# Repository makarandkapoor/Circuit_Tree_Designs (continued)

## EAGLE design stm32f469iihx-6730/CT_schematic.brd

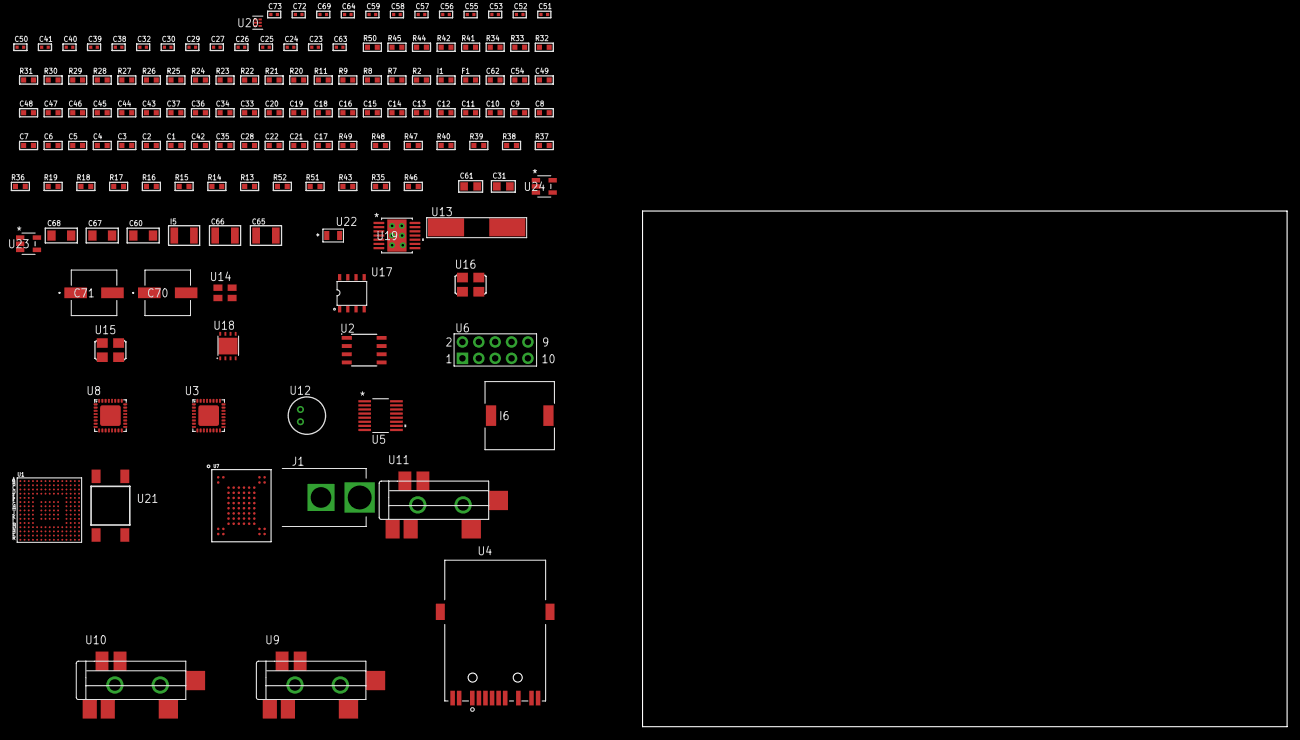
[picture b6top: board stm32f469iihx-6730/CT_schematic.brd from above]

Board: 2 copper layers, 100.0 x 80.0 mm, 147 parts (0 on the bottom side), 111 nets, no tracks yet.

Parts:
C1, C19, C33, C34, C36, C37, C43, C44, C45, C46, C47, C48, C49, C54, C62: 1e-06; C0603
C2, C3, C4, C5, C6, C7, C8, C9, C10, C11, C12, C13, C14, C15, C16, C20: 1e-07; C0603
C17: 4.7e-06; C0603
C18: 1e-08; C0603
C21, C22, C28, C42: 2.2e-06; C0603
C23, C24: 1e-11; C0402
C25, C55, C56, C57, C58, C59, C72, C73: 1e-08; C0402
C26, C27, C29, C30, C32, C38, C39, C40, C41, C50, C51, C52, C53, C64, C69: 1e-07; C0402
C31, C61: 1e-05; C0805
C35: 2.2e-07; C0603
C60, C67, C68: 1e-05; C1206
C63: 3.3e-09; C0402
C65, C66: 2.2e-05; C1210
C70, C71: 0.0001; EXV-9H
F1: 240.0; L0603
I1: 97.0; R0603
I5: 1e-05; L1210
I6: 5.2e-06; DR1040
J1: PJ-037B; PJ-037B_PACKAGE
R2, R29, R31, R32, R33, R34, R45: 1000.0; R0603
R7, R8, R25, R26, R27, R28, R30: 4700.0; R0603
R9, R11: 2200.0; R0603
R13, R14, R15, R16, R17, R18, R19, R36, R37, R38, R39, R40, R48, R49: 10000.0; R0603
R20, R21: 0.1; R0603
R22, R44: 200.0; R0603
R23: 220.0; R0603
R24: 6490.0; R0603
R35, R43: 100000.0; R0603
R41, R42: 1270.0; R0603
R46: 71007.101651032; R0603
R47: 22000.0; R0603
R50: 9100.0; R0603
R51: 680000.0; R0603
R52: 120000.0; R0603
U1: STM32F469IIH6; UFBGA176
U2: AT25020B-SSHL-T; SOIC-8
U3: KSZ8081RNBIA-TR; QFN-32
U4: 7498011122R
U5: LTC2804CGN-1#PBF; SSOP-16
U6: HTSS-105-01-G-D
U7: mt29f4g08abadah4; VFBGA-63
U8: SGTL5000XNAA3; QFN-32
U9, U10, U11: SJ-43515TS-SMT-TR
U12: WM-64PCT; WM-64PC
U13: ABLS-25.000MHZ-B2F-T
U14: ASEK-32.768KHz-ECST; ASEK
U15: ASFL-24.57MHZ-NCS; ASFL1
U16: ASFL1-50MHZ-NCS; ASFL1
U17: idt74fct38072; IDT74FCT38072
U18: LP3878SDX-ADJ/NOPB; WSON-8
U19: tps54225PWP; HTSSOP14
U20: TPS3895ADRYR; SON-6
U21: 4-1437565-2; SW_4-1437565-2
U22: Q65110A2395; LGM67K-G1J2-24-Z
U23, U24: nc7sz125m5x; NC7SZ125M5X

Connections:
CLK_CRYSTAL_U1_G1: C23.1, U1.G1, U13.1
CLK_CRYSTAL_U1_H1: C24.1, U1.H1, U13.2
CLK_U1_E1: U1.E1, U14.3
CLK_U1_N2: U1.N2, U17.7
CLK_U3_9: U3.9, U17.6
CLK_U8_21: U8.21, U15.3
CLK_U17_3: U16.3, U17.3
GND: C1.2, C2.2, C3.2, C4.2, C5.2, C6.2, C7.2, C8.2, C9.2, C10.2, C11.2, C12.2, C13.2, C14.2, C15.2, C16.2, C17.2, C18.2, C19.2, C20.2, C21.2, C22.2, C23.2, C24.2, C25.2, C26.2, C27.2, C28.2, C29.2, C30.2, C31.2, C32.2, C33.2, C34.2, C36.2, C37.2, C38.2, C39.2, C40.2, C41.2, C42.2, C50.2, C51.2, C52.2, C53.2, C54.2, C55.2, C56.2, C57.2, C58.2, C59.2, C60.2, C61.2, C62.2, C63.2, C65.2, C66.2, C67.2, C68.2, C69.2, C70.2, C71.2, C72.2, C73.2, J1.2, R2.2, R15.2, R16.2, R20.2, R21.2, R24.2, R26.2, R29.2, R31.2, R32.2, R33.2, R34.2, R42.2, R45.2, R47.2, R50.2, R52.2, U1.D5, U1.D7, U1.D8, U1.D9, U1.F2, U1.F6, U1.F7, U1.F8, U1.F9, U1.F10, U1.F12, U1.G2, U1.G6, U1.G7, U1.G8, U1.G9, U1.G10, U1.G12, U1.H6, U1.H7, U1.H8, U1.H9, U1.H10, U1.H12, U1.J6, U1.J7, U1.J8, U1.J9, U1.J10, U1.K6, U1.K7, U1.K8, U1.K9, U1.K10, U1.M1, U1.M8, U1.M9, U1.N1, U2.4, U3.1, U3.EXP, U4.1, U4.10, U5.8, U6.9, U7.C5, U7.F7, U7.K3, U7.K8, U8.1, U8.3, U8.7, U8.EXP, U10.1, U11.1, U12.2, U14.2, U15.2, U16.2, U17.4, U17.5, U17.8, U18.3, U18.PAD, U19.5, U19.8, U19.9, U19.15, U20.2, U22.C, U23.1, U23.3, U24.1, U24.3
NET_U1_C6: R13.1, U1.C6
NET_U1_D6: R14.1, U1.D6
NET_U1_F13: C22.1, U1.F13
NET_U1_J1: R8.1, U1.J1, U24.4
NET_U1_L4: R16.1, U1.L4
NET_U1_M3: R9.1, U1.M3, U3.12
NET_U1_M6: R15.1, U1.M6
NET_U1_M10: C21.1, U1.M10
NET_U1_P2: R11.1, U1.P2, U3.11
NET_U1_R1: C18.1, C19.1, F1.1, U1.P1, U1.R1
NET_U1_R15: U21.3, U21.4
NET_U2_3: R17.1, U2.3
NET_U2_7: R19.1, U2.7
NET_U3_2: C28.1, C29.1, U3.2
NET_U3_3: C30.1, I1.1, U3.3
NET_U3_10: R24.1, U3.10
NET_U3_13: R27.1, U3.13
NET_U3_14: R28.1, U3.14
NET_U3_19: R26.1, U3.19
NET_U3_20: R32.1, U3.20
NET_U3_21: R25.1, U3.21
NET_U3_28: R30.1, U3.28
NET_U3_29: R31.1, U3.29
NET_U3_31: R33.1, U3.31
NET_U3_32: R7.1, U3.32, U23.4
NET_U4_1: U3.7, U4.1
NET_U4_2: C26.1, U4.2
NET_U4_3: U3.6, U4.3
NET_U4_4: U3.5, U4.4
NET_U4_5: C27.1, U4.5
NET_U4_6: U3.4, U4.6
NET_U4_8: R21.1, U4.8
NET_U4_9: R22.1, U4.9
NET_U4_12: R23.1, U4.12
NET_U4_13: R20.1, U4.13, U4.14
NET_U5_6: C33.1, U5.6
NET_U5_7: C35.1, I5.2, U5.7
NET_U5_9: C34.1, U5.9
NET_U5_10: C35.2, U5.10
NET_U5_11: R35.1, U5.11
NET_U6_3: U5.1, U6.3
NET_U6_4: U5.2, U6.4
NET_U6_5: U5.3, U6.5
NET_U6_6: U5.4, U6.6
NET_U7_C3: R40.1, U7.C3
NET_U8_10: C53.1, U8.10
NET_U8_29: R41.1, U8.29
NET_U8_31: R42.1, U8.31
NET_U9_1: U8.4, U9.1
NET_U9_2: U8.2, U9.2
NET_U9_5: U8.6, U9.5
NET_U10_2: C44.1, U10.2
NET_U10_5: C43.1, U10.5
NET_U11_2: C46.1, C47.1, U11.2
NET_U11_5: C45.1, U11.5
NET_U11_13: C46.2, C47.2
NET_U12_1: C48.1, C49.1, C54.1, U8.16, U12.1
NET_U12_15: C48.2, C49.2
NET_U18_1: C59.1, U18.1
NET_U18_6: R44.2, R45.1, U18.6
NET_U18_8: R43.1, U18.8
NET_U19_2: R46.2, R47.1, U19.2
NET_U19_3: C62.1, U19.3
NET_U19_4: C63.1, U19.4
NET_U19_10: C64.1, I6.1, U19.10, U19.11
NET_U19_12: C64.2, U19.12
NET_U20_1: R49.1, R50.1, U20.1
NET_U20_3: R51.2, R52.1, U20.3
NET_U20_4: R48.1, U20.4, U23.2, U24.2
NET_U21_1: R2.1, U21.1, U21.2
PROC_ETH_CRS_DV: U1.R3, U3.18
PROC_ETH_RXD0: R34.1, U1.N5, U3.16
PROC_ETH_RXD1: R29.1, U1.P5, U3.15
PROC_ETH_TXD0: U1.A8, U3.24
PROC_ETH_TXD1: U1.A7, U3.25
PROC_ETH_TX_EN: U1.B9, U3.23
PROC_FMC_A16: U1.N14, U7.D5
PROC_FMC_A17: U1.N13, U7.C4
PROC_FMC_D0: U1.M14, U7.H4
PROC_FMC_D1: U1.L14, U7.J4
PROC_FMC_D2: U1.B12, U7.K4
PROC_FMC_D3: U1.C12, U7.K5
PROC_FMC_D4: U1.R8, U7.K6
PROC_FMC_D5: U1.P8, U7.J7
PROC_FMC_D6: U1.P9, U7.K7
PROC_FMC_D7: U1.R9, U7.J8
PROC_FMC_INT: R36.1, U1.J14, U7.C8
PROC_FMC_NCE: R37.1, U1.C10, U7.C6
PROC_FMC_NOE: R39.1, U1.D10, U7.D4
PROC_FMC_NWE: R38.1, U1.C11, U7.C7
PROC_I2S2_CK: U1.D11, U8.24
PROC_I2S2_EXT_SD: U1.M4, U8.25
PROC_I2S2_SD: U1.C13, U8.26
PROC_I2S2_WS: U1.B4, U8.23
PROC_SPI1_MISO: U1.A9, U2.2
PROC_SPI1_MOSI: U1.A6, U2.5
PROC_SPI1_NSS: R18.1, U1.A13, U2.1
PROC_SPI1_SCK: U1.A10, U2.6
PROC_UART4_RX: U1.B13, U5.16
PROC_UART4_TX: U1.B14, U5.14
VCC_S1_7V4: C60.1, C67.1, C68.1, C70.1, C71.1, J1.1, R43.2, U18.4, U19.7, U19.13, U19.14
VCC_TIER1_1V2: C50.1, C61.1, R44.1, U8.30, U18.5
VCC_TIER1_3V3: C1.1, C2.1, C3.1, C4.1, C5.1, C6.1, C7.1, C8.1, C9.1, C10.1, C11.1, C12.1, C13.1, C14.1, C15.1, C16.1, C17.1, C20.1, C25.1, C31.1, C32.1, C36.1, C37.1, C38.1, C39.1, C40.1, C41.1, C42.1, C51.1, C52.1, C55.1, C56.1, C57.1, C58.1, C65.1, C66.1, C69.1, C72.1, C73.1, F1.2, I1.2, I5.1, I6.2, R7.2, R8.2, R9.2, R11.2, R13.2, R14.2, R17.2, R18.2, R19.2, R25.2, R27.2, R28.2, R30.2, R35.2, R36.2, R37.2, R38.2, R39.2, R40.2, R41.2, R46.1, R48.2, R49.2, R51.1, U1.C1, U1.C5, U1.C7, U1.C8, U1.C9, U1.F3, U1.G3, U1.G13, U1.H13, U1.J12, U1.J13, U1.K4, U1.N8, U1.N9, U1.N10, U2.8, U3.17, U5.5, U5.12, U7.D3, U7.G4, U7.H8, U7.J6, U8.5, U8.20, U14.4, U15.4, U16.4, U17.1, U17.2, U19.1, U20.6, U23.5, U24.5

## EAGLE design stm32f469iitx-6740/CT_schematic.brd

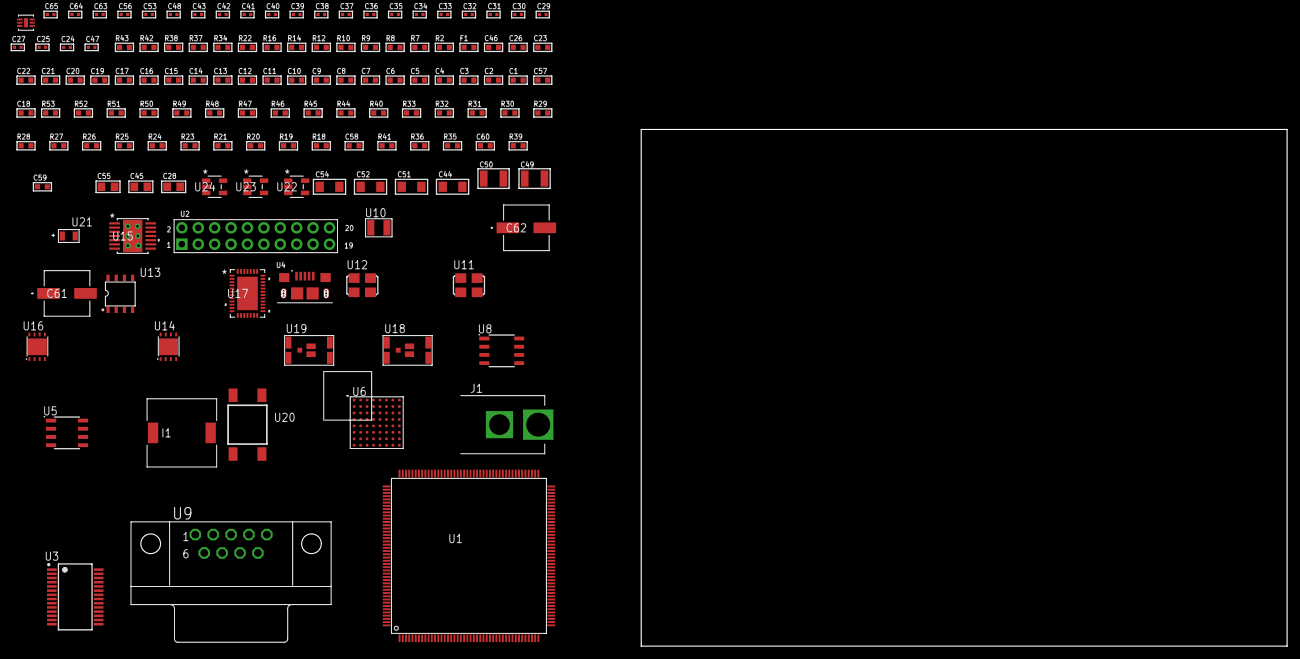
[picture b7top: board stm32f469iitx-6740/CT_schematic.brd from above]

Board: 2 copper layers, 136 parts (0 on the bottom side), 131 nets, no tracks yet.

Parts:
C1, C20, C26, C46: 1e-06; C0603
C2, C3, C4, C5, C6, C7, C8, C9, C10, C11, C12, C13, C14, C15, C16, C17, C21, C22, C23: 1e-07; C0603
C18: 4.7e-06; C0603
C19: 1e-08; C0603
C24, C25: 1e-11; C0402
C27, C29, C30, C32, C34, C36, C38, C39, C48, C56: 1e-07; C0402
C28: 4.7e-06; C0805
C31, C33, C35, C37, C40, C41, C42, C43, C53, C63, C64, C65: 1e-08; C0402
C44, C51, C52, C54: 1e-05; C1206
C45, C55: 1e-05; C0805
C47: 3.3e-09; C0402
C49, C50: 2.2e-05; C1210
C57: 2.2e-06; C0603
C58: 2.45e-08; R0603
C59: 2.8258362168397e-09; R0603
C60: 7.105e-09; R0603
C61, C62: 0.0001; EXV-9H
F1: 240.0; L0603
I1: 5.2e-06; DR1040
J1: PJ-037B; PJ-037B_PACKAGE
R2, R38, R43: 1000.0; R0603
R7, R8, R9, R22: 4700.0; R0603
R10, R12, R14, R16: 2200.0; R0603
R18, R19, R20, R21, R23, R24, R25, R26, R27, R28, R29, R30, R31, R32, R33, R44, R46, R47, R50, R51, R52: 10000.0; R0603
R34: 120.0; R0603
R35: 470000.0; R0603
R36, R41: 100000.0; R0603
R37, R42: 200.0; R0603
R39: 71007.101651032; R0603
R40: 22000.0; R0603
R45: 75000.0; R0603
R48, R49: 95300.0; R0603
R53: 62000.0; R0603
U1: STM32F469IIT6; LQFP176
U2: arducam_ov2640; ARDUCAM
U3: FT232RL-REEL; SSOP-28
U4: 10118193-0001LF; FCI_10118193-0001LF
U5: AT24C02D-SSHM-T; AT24C02D
U6: PC28F512P33BFD
U7: SI7006-A20-IM; DFN-6
U8: SN65HVD230D; SOIC-8
U9: 182-009-113R531; 182-009-MALE
U10: ABS07-32.768KHZ-7-T
U11: ASFL1-12MHZ-NCS; ASFL1
U12: ASFL1-25MHZ-NCS; ASFL1
U13: idt74fct38072; IDT74FCT38072
U14, U16: LP3878SDX-ADJ/NOPB; WSON-8
U15: tps54225PWP; HTSSOP14
U17: LTC2928CUHF#PBF; QFN-38_UHF
U18, U19: IRF8306MTRPbF; IRF8306MTRPBF
U20: 4-1437565-2; SW_4-1437565-2
U21: Q65110A2395; LGM67K-G1J2-24-Z
U22, U23, U24: nc7sz125m5x; NC7SZ125M5X

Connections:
CLK_CRYSTAL_U1_9: C24.1, U1.9, U10.1
CLK_CRYSTAL_U1_10: C25.1, U1.10, U10.2
CLK_U1_29: U1.29, U13.6
CLK_U2_8: U2.8, U13.7
CLK_U3_27: U3.27, U11.3
CLK_U13_3: U12.3, U13.3
GND: C1.2, C2.2, C3.2, C4.2, C5.2, C6.2, C7.2, C8.2, C9.2, C10.2, C11.2, C12.2, C13.2, C14.2, C15.2, C16.2, C17.2, C18.2, C19.2, C20.2, C21.2, C22.2, C23.2, C24.2, C25.2, C26.2, C27.2, C28.2, C29.2, C30.2, C31.2, C32.2, C33.2, C34.2, C35.2, C36.2, C37.2, C38.2, C39.2, C40.2, C41.2, C42.2, C43.2, C44.2, C45.2, C46.2, C47.2, C49.2, C50.2, C51.2, C52.2, C53.2, C54.2, C55.2, C56.2, C57.2, C58.2, C59.2, C60.2, C61.2, C62.2, C63.2, C64.2, C65.2, J1.2, R2.2, R20.2, R24.2, R25.2, R27.2, R28.2, R35.2, R38.2, R40.2, R43.2, R45.2, R48.2, R49.2, R50.2, R51.2, R52.2, U1.14, U1.22, U1.37, U1.61, U1.71, U1.95, U1.103, U1.109, U1.117, U1.130, U1.135, U1.148, U1.158, U2.2, U2.20, U3.7, U3.18, U3.21, U3.25, U3.26, U4.5, U4.6, U4.7, U4.8, U4.9, U5.4, U6.B2, U6.H2, U6.H4, U6.H6, U7.2, U7.7, U8.2, U9.5, U11.2, U12.2, U13.4, U13.5, U13.8, U14.3, U14.PAD, U15.5, U15.8, U15.9, U15.15, U16.3, U16.PAD, U17.8, U17.9, U17.10, U17.12, U17.13, U17.24, U17.25, U17.30, U17.32, U17.39, U21.C, U22.1, U22.3, U23.1, U23.3, U24.1, U24.3
NET_U1_31: R8.1, U1.31, U23.4
NET_U1_39: C19.1, C20.1, F1.1, U1.38, U1.39
NET_U1_45: R14.1, U1.45, U5.6
NET_U1_46: R16.1, U1.46, U5.5
NET_U1_48: R21.1, U1.48
NET_U1_58: R20.1, U1.58
NET_U1_129: C23.1, U1.129
NET_U1_166: R19.1, U1.166
NET_U1_167: R10.1, U1.167, U7.6
NET_U1_168: R12.1, U1.168, U7.1
NET_U1_171: R18.1, U1.171
NET_U1_174: U20.3, U20.4
NET_U2_19: R9.1, U2.19, U24.4
NET_U3_14: R23.1, U3.14
NET_U3_17: C29.1, U3.17
NET_U3_19: R24.1, U3.19
NET_U4_1: R22.1, U4.1
NET_U4_2: U3.16, U4.2
NET_U4_3: U3.15, U4.3
NET_U5_1: R26.1, U5.1
NET_U5_2: R27.1, U5.2
NET_U5_3: R28.1, U5.3
NET_U5_7: R25.1, U5.7
NET_U6_A4: C36.1, C37.1, U6.A4
NET_U6_C6: R32.1, U6.C6
NET_U6_D4: R7.1, U6.D4, U22.4
NET_U8_6: R34.2, U8.6
NET_U8_8: R35.1, U8.8
NET_U9_2: R34.2, U8.6, U9.2
NET_U9_3: R34.1, U8.7, U9.3
NET_U14_1: C43.1, U14.1
NET_U14_6: R37.2, R38.1, U14.6
NET_U14_8: R36.1, U14.8
NET_U15_2: R39.2, R40.1, U15.2
NET_U15_3: C46.1, U15.3
NET_U15_4: C47.1, U15.4
NET_U15_10: C48.1, I1.1, U15.10, U15.11
NET_U15_12: C48.2, U15.12
NET_U16_1: C53.1, U16.1
NET_U16_6: R42.2, R43.1, U16.6
NET_U16_8: R41.1, U16.8
NET_U17_3: R51.1, U17.3
NET_U17_6: R48.1, U17.6
NET_U17_7: R49.1, U17.7
NET_U17_16: R50.1, R53.1, U17.16
NET_U17_18: R47.1, U17.18
NET_U17_19: R46.1, U17.19, U17.20
NET_U17_21: R44.1, R45.1, U17.21, U22.2, U23.2, U24.2
NET_U17_22: C56.1, R44.2, R46.2, R47.2, U17.11, U17.22
NET_U17_26: C59.1, U17.26
NET_U17_27: C58.1, U17.27
NET_U17_28: C60.1, U17.28
NET_U17_38: R52.1, U17.38
NET_U18_3: U17.2, U18.3
NET_U19_3: U17.37, U19.3
NET_U20_1: R2.1, U20.1, U20.2
PROC_CAN1_RX: U1.11, U8.4
PROC_CAN1_TX: U1.127, U8.1
PROC_DCMI_D0: U1.119, U2.18
PROC_DCMI_D1: U1.120, U2.17
PROC_DCMI_D2: U1.121, U2.16
PROC_DCMI_D3: U1.122, U2.15
PROC_DCMI_D4: U1.140, U2.14
PROC_DCMI_D5: U1.164, U2.13
PROC_DCMI_D6: U1.175, U2.12
PROC_DCMI_D7: U1.176, U2.11
PROC_DCMI_D8: U1.83, U2.10
PROC_DCMI_D9: U1.84, U2.9
PROC_DCMI_HSYNC: U1.50, U2.6
PROC_DCMI_PIXCLK: U1.52, U2.7
PROC_DCMI_VSYNC: U1.152, U2.5
PROC_FMC_A0: U1.16, U6.A1
PROC_FMC_A1: U1.17, U6.B1
PROC_FMC_A2: U1.18, U6.C1
PROC_FMC_A3: U1.19, U6.D1
PROC_FMC_A4: U1.20, U6.D2
PROC_FMC_A5: U1.21, U6.A2
PROC_FMC_A6: U1.60, U6.C2
PROC_FMC_A7: U1.63, U6.A3
PROC_FMC_A8: U1.64, U6.B3
PROC_FMC_A9: U1.65, U6.C3
PROC_FMC_A10: U1.66, U6.D3
PROC_FMC_A11: U1.67, U6.C4
PROC_FMC_A12: U1.110, U6.A5
PROC_FMC_A13: U1.111, U6.B5
PROC_FMC_A14: U1.112, U6.C5
PROC_FMC_A15: U1.113, U6.D7
PROC_FMC_A16: U1.92, U6.D8
PROC_FMC_A17: U1.93, U6.A7
PROC_FMC_A18: U1.94, U6.B7
PROC_FMC_A19: U1.2, U6.C7
PROC_FMC_A20: U1.3, U6.C8
PROC_FMC_A21: U1.4, U6.A8
PROC_FMC_A22: U1.5, U6.G1
PROC_FMC_A23: U1.1, U6.H8
PROC_FMC_A24: U1.156, U6.B6
PROC_FMC_CLK: U1.145, U6.E6
PROC_FMC_D0: U1.97, U6.F2
PROC_FMC_D1: U1.98, U6.E2
PROC_FMC_D2: U1.142, U6.G3
PROC_FMC_D3: U1.143, U6.E4
PROC_FMC_D4: U1.68, U6.E5
PROC_FMC_D5: U1.69, U6.G5
PROC_FMC_D6: U1.70, U6.G6
PROC_FMC_D7: U1.73, U6.H7
PROC_FMC_D8: U1.74, U6.E1
PROC_FMC_D9: U1.75, U6.E3
PROC_FMC_D10: U1.76, U6.F3
PROC_FMC_D11: U1.77, U6.F4
PROC_FMC_D12: U1.78, U6.F5
PROC_FMC_D13: U1.89, U6.H5
PROC_FMC_D14: U1.90, U6.G7
PROC_FMC_D15: U1.91, U6.E7
PROC_FMC_NE2: R30.1, U1.155, U6.B4
PROC_FMC_NL: R29.1, U1.165, U6.F6
PROC_FMC_NOE: R31.1, U1.146, U6.F8
PROC_FMC_NWAIT: U1.150, U6.F7
PROC_FMC_NWE: R33.1, U1.147, U6.G8
VCC_8V0: C57.1, C61.1, C62.1, J1.1, R53.2, U17.23, U18.1, U18.2, U18.6, U18.7, U19.1, U19.2, U19.6, U19.7
VCC_S1_8V0: C44.1, C51.1, C52.1, R36.2, U14.4, U15.7, U15.13, U15.14, U18.4, U18.5
VCC_S2_8V0: C54.1, R41.2, U16.4, U19.4, U19.5
VCC_TIER1_1V2: C22.1, C45.1, R37.1, U1.81, U14.5
VCC_TIER1_3V3: C1.1, C2.1, C3.1, C4.1, C5.1, C6.1, C7.1, C8.1, C9.1, C10.1, C11.1, C12.1, C13.1, C14.1, C15.1, C16.1, C17.1, C18.1, C21.1, C26.1, C27.1, C28.1, C30.1, C31.1, C32.1, C33.1, C34.1, C35.1, C38.1, C39.1, C40.1, C41.1, C42.1, C49.1, C50.1, C63.1, C64.1, C65.1, F1.2, I1.2, R7.2, R8.2, R9.2, R10.2, R12.2, R14.2, R16.2, R18.2, R19.2, R21.2, R23.2, R26.2, R29.2, R30.2, R31.2, R32.2, R33.2, R39.1, U1.6, U1.15, U1.23, U1.36, U1.49, U1.62, U1.72, U1.82, U1.96, U1.99, U1.118, U1.131, U1.136, U1.149, U1.159, U1.172, U2.1, U3.4, U3.20, U5.8, U6.A6, U6.D5, U6.D6, U6.G4, U6.H3, U7.5, U8.3, U11.4, U12.4, U13.1, U13.2, U15.1, U22.5, U23.5, U24.5
VCC_TIER2_1V2: C55.1, R42.1, U16.5

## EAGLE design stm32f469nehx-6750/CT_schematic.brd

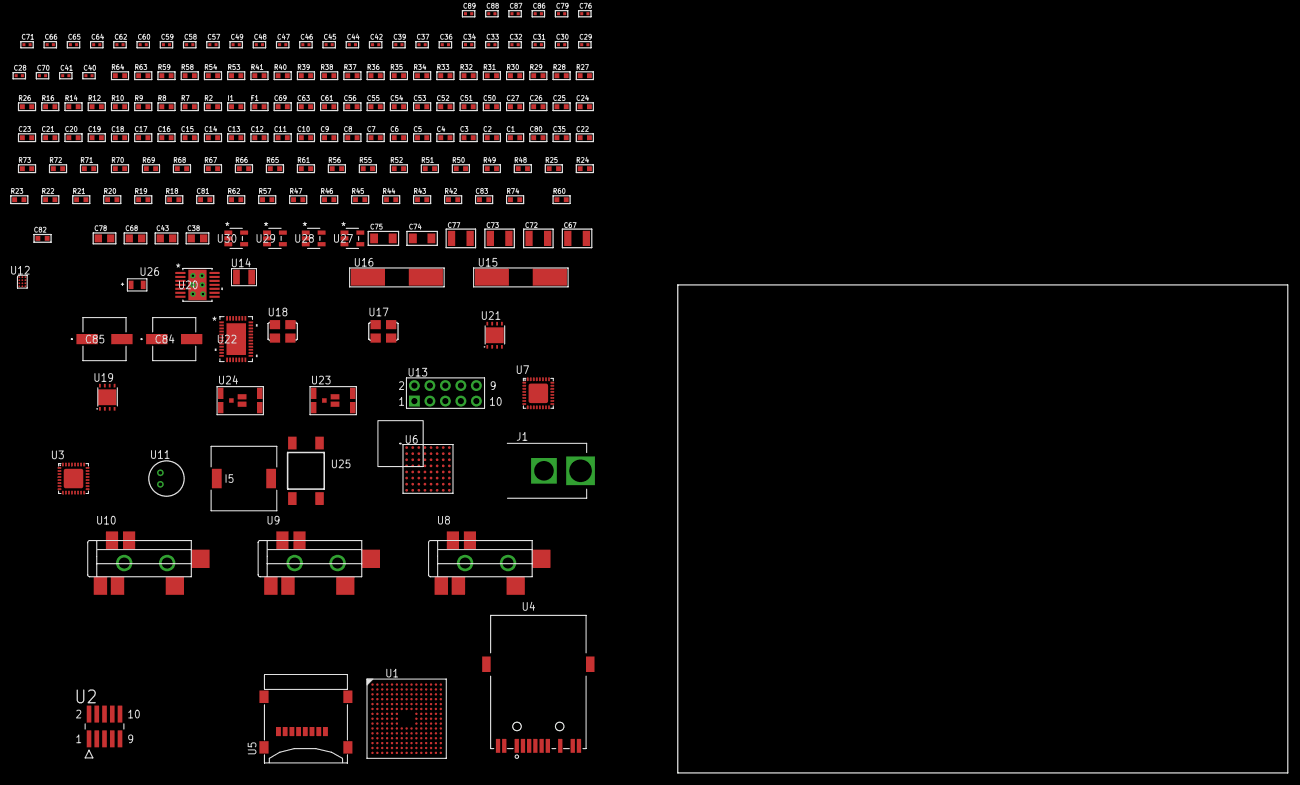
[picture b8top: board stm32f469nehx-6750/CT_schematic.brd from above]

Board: 2 copper layers, 100.0 x 80.0 mm, 188 parts (0 on the bottom side), 166 nets, no tracks yet.

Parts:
C1, C24, C50, C51, C52, C53, C54, C55, C56, C61, C63, C69: 1e-06; C0603
C2, C3, C4, C5, C6, C7, C8, C9, C10, C11, C12, C13, C14, C15, C16, C17, C18, C19, C20, C21, C25, C26, C27: 1e-07; C0603
C22: 4.7e-06; C0603
C23: 1e-08; C0603
C28, C29, C30, C31: 1e-11; C0402
C32, C33, C34, C36, C37, C39, C42, C44, C46, C48, C57, C58, C59, C60, C62, C71, C79: 1e-07; C0402
C35, C80: 2.2e-06; C0603
C38, C43, C68, C78: 1e-05; C0805
C40, C41: 2.2e-11; C0402
C45, C47, C49, C64, C65, C66, C76, C86, C87, C88, C89: 1e-08; C0402
C67, C77: 1e-05; C1210
C70: 3.3e-09; C0402
C72, C73: 2.2e-05; C1210
C74, C75: 1e-05; C1206
C81: 2.45e-08; R0603
C82: 2.8258362168397e-09; R0603
C83: 7.105e-09; R0603
C84, C85: 0.0001; EXV-9H
F1: 240.0; L0603
I1: 97.0; R0603
I5: 7e-06; DR1040
J1: PJ-037B; PJ-037B_PACKAGE
R2, R36, R38, R39, R41, R59, R64: 1000.0; R0603
R7, R8, R9, R32, R33, R34, R35, R37, R40: 4700.0; R0603
R10, R12, R14, R16: 2200.0; R0603
R18, R19, R20, R21, R22, R23, R24, R25, R48, R49, R50, R51, R52, R55, R56, R65, R67, R68, R71, R72, R73: 10000.0; R0603
R26: 5.0; R0603
R27, R28: 0.1; R0603
R29, R58, R63: 200.0; R0603
R30: 220.0; R0603
R31: 6490.0; R0603
R42, R43, R44, R45, R46, R47, R57, R62: 100000.0; R0603
R53, R54: 1270.0; R0603
R60: 71007.101651032; R0603
R61: 22000.0; R0603
R66: 75000.0; R0603
R69, R70: 95300.0; R0603
R74: 111363.63636364; R0603
U1: STM32F469NEH6; TFBGA216
U2: FTSH-105-01-L-DV-K; SAMTEC_FTSH-105-01-L-DV-K
U3: KSZ8081RNBIA-TR; QFN-32
U4: 7498011122R
U5: 0472192001; MOLEX_47219-2001
U6: PC28F512P33BFD
U7: SGTL5000XNAA3; QFN-32
U8, U9, U10: SJ-43515TS-SMT-TR
U11: WM-64PCT; WM-64PC
U12: TSC2014IYZGT
U13: HTSS-105-01-G-D
U14: ABS07-32.768KHZ-7-T
U15, U16: ABLS-25.000MHZ-B2F-T
U17: ASFL-24.57MHZ-NCS; ASFL1
U18: ASFL1-50MHZ-NCS; ASFL1
U19, U21: LP3878SDX-ADJ/NOPB; WSON-8
U20: tps54225PWP; HTSSOP14
U22: LTC2928CUHF#PBF; QFN-38_UHF
U23, U24: IRF8306MTRPbF; IRF8306MTRPBF
U25: 4-1437565-2; SW_4-1437565-2
U26: Q65110A2395; LGM67K-G1J2-24-Z
U27, U28, U29, U30: nc7sz125m5x; NC7SZ125M5X

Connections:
CLK_CRYSTAL_U1_E1: C28.1, U1.E1, U14.1
CLK_CRYSTAL_U1_F1: C29.1, U1.F1, U14.2
CLK_CRYSTAL_U1_G1: C30.1, U1.G1, U15.1
CLK_CRYSTAL_U1_H1: C31.1, U1.H1, U15.2
CLK_CRYSTAL_U3_8: C40.1, U3.8, U16.2
CLK_CRYSTAL_U3_9: C41.1, U3.9, U16.1
CLK_U1_N2: U1.N2, U18.3
CLK_U7_21: U7.21, U17.3
GND: C1.2, C2.2, C3.2, C4.2, C5.2, C6.2, C7.2, C8.2, C9.2, C10.2, C11.2, C12.2, C13.2, C14.2, C15.2, C16.2, C17.2, C18.2, C19.2, C20.2, C21.2, C22.2, C23.2, C24.2, C25.2, C26.2, C27.2, C28.2, C29.2, C30.2, C31.2, C32.2, C33.2, C34.2, C35.2, C36.2, C37.2, C38.2, C39.2, C40.2, C41.2, C42.2, C43.2, C44.2, C45.2, C46.2, C47.2, C48.2, C49.2, C57.2, C58.2, C59.2, C60.2, C61.2, C62.2, C63.2, C64.2, C65.2, C66.2, C67.2, C68.2, C69.2, C70.2, C72.2, C73.2, C74.2, C75.2, C76.2, C77.2, C78.2, C79.2, C80.2, C81.2, C82.2, C83.2, C84.2, C85.2, C86.2, C87.2, C88.2, C89.2, J1.2, R2.2, R20.2, R25.2, R26.2, R27.2, R28.2, R31.2, R33.2, R36.2, R38.2, R39.2, R41.2, R54.2, R59.2, R61.2, R64.2, R66.2, R69.2, R70.2, R71.2, R72.2, R73.2, U1.F2, U1.F6, U1.F7, U1.F8, U1.F9, U1.F10, U1.G6, U1.G10, U1.G12, U1.H6, U1.H10, U1.J6, U1.J10, U1.K6, U1.K7, U1.K8, U1.K9, U1.K10, U1.L6, U1.M1, U1.N1, U2.3, U2.5, U3.1, U3.EXP, U4.1, U4.10, U5.6, U5.G1, U5.G2, U5.G3, U5.G4, U6.B2, U6.H2, U6.H4, U6.H6, U7.1, U7.3, U7.7, U7.EXP, U9.1, U10.1, U11.2, U12.B2, U12.D2, U13.9, U17.2, U18.2, U19.3, U19.PAD, U20.5, U20.8, U20.9, U20.15, U21.3, U21.PAD, U22.8, U22.9, U22.10, U22.12, U22.13, U22.24, U22.25, U22.30, U22.32, U22.39, U26.C, U27.2, U27.3, U28.1, U28.3, U29.1, U29.3, U30.1, U30.3
NET_U1_A7: R10.1, U1.A7, U12.D1
NET_U1_B4: R12.1, U1.B4, U12.C1
NET_U1_E5: R18.1, U1.E5
NET_U1_E6: R19.1, U1.E6
NET_U1_E11: C27.1, U1.E11
NET_U1_J1: R9.1, U1.J1, U30.4
NET_U1_L5: R21.1, U1.L5
NET_U1_M3: R14.1, U1.M3, U3.12
NET_U1_M5: R20.1, U1.M5
NET_U1_P2: R16.1, U1.P2, U3.11
NET_U1_R1: C23.1, C24.1, F1.1, U1.P1, U1.R1
NET_U1_R15: U25.3, U25.4
NET_U2_9: R26.1, U2.9
NET_U3_2: C35.1, C36.1, U3.2
NET_U3_3: C37.1, I1.1, U3.3
NET_U3_10: R31.1, U3.10
NET_U3_13: R34.1, U3.13
NET_U3_14: R35.1, U3.14
NET_U3_19: R33.1, U3.19
NET_U3_20: R39.1, U3.20
NET_U3_21: R32.1, U3.21
NET_U3_28: R37.1, U3.28
NET_U3_29: R38.1, U3.29
NET_U3_31: R40.1, U3.31
NET_U3_32: R7.1, U3.32, U28.4
NET_U4_1: U3.7, U4.1
NET_U4_2: C33.1, U4.2
NET_U4_3: U3.6, U4.3
NET_U4_4: U3.5, U4.4
NET_U4_5: C34.1, U4.5
NET_U4_6: U3.4, U4.6
NET_U4_8: R28.1, U4.8
NET_U4_9: R29.1, U4.9
NET_U4_12: R30.1, U4.12
NET_U4_13: R27.1, U4.13, U4.14
NET_U6_A4: C48.1, C49.1, U6.A4
NET_U6_C6: R51.1, U6.C6
NET_U6_D4: R8.1, U6.D4, U29.4
NET_U7_10: C60.1, U7.10
NET_U7_29: R53.1, U7.29
NET_U7_31: R54.1, U7.31
NET_U8_1: U7.4, U8.1
NET_U8_2: U7.2, U8.2
NET_U8_5: U7.6, U8.5
NET_U9_2: C51.1, U9.2
NET_U9_5: C50.1, U9.5
NET_U10_2: C53.1, C54.1, U10.2
NET_U10_5: C52.1, U10.5
NET_U10_13: C53.2, C54.2
NET_U11_1: C55.1, C56.1, C61.1, U7.16, U11.1
NET_U11_15: C55.2, C56.2
NET_U12_B1: R56.1, U12.B1
NET_U12_C2: R55.1, U12.C2
NET_U13_3: U12.B3, U13.3
NET_U13_4: U12.D3, U13.4
NET_U13_5: U12.A3, U13.5
NET_U13_6: U12.C3, U13.6
NET_U19_1: C66.1, U19.1
NET_U19_6: R58.2, R59.1, U19.6
NET_U19_8: R57.1, U19.8
NET_U20_2: R60.2, R61.1, U20.2
NET_U20_3: C69.1, U20.3
NET_U20_4: C70.1, U20.4
NET_U20_10: C71.1, I5.1, U20.10, U20.11
NET_U20_12: C71.2, U20.12
NET_U21_1: C76.1, U21.1
NET_U21_6: R63.2, R64.1, U21.6
NET_U21_8: R62.1, U21.8
NET_U22_3: R72.1, U22.3
NET_U22_6: R69.1, U22.6
NET_U22_7: R70.1, U22.7
NET_U22_16: R71.1, R74.1, U22.16
NET_U22_18: R68.1, U22.18
NET_U22_19: R67.1, U22.19, U22.20
NET_U22_21: R65.1, R66.1, U22.21, U27.4, U28.2, U29.2, U30.2
NET_U22_22: C79.1, R65.2, R67.2, R68.2, U22.11, U22.22
NET_U22_26: C82.1, U22.26
NET_U22_27: C81.1, U22.27
NET_U22_28: C83.1, U22.28
NET_U22_38: R73.1, U22.38
NET_U23_3: U22.2, U23.3
NET_U24_3: U22.37, U24.3
NET_U25_1: R2.1, U25.1, U25.2
PROC_ETH_CRS_DV: U1.R3, U3.18
PROC_ETH_RXD0: R41.1, U1.N5, U3.16
PROC_ETH_RXD1: R36.1, U1.P5, U3.15
PROC_ETH_TXD0: U1.L13, U3.24
PROC_ETH_TXD1: U1.A4, U3.25
PROC_ETH_TX_EN: U1.B8, U3.23
PROC_FMC_A0: U1.D2, U6.A1
PROC_FMC_A1: U1.E2, U6.B1
PROC_FMC_A2: U1.G2, U6.C1
PROC_FMC_A3: U1.H2, U6.D1
PROC_FMC_A4: U1.J2, U6.D2
PROC_FMC_A5: U1.K3, U6.A2
PROC_FMC_A6: U1.M6, U6.C2
PROC_FMC_A7: U1.N6, U6.A3
PROC_FMC_A8: U1.P6, U6.B3
PROC_FMC_A9: U1.M8, U6.C3
PROC_FMC_A10: U1.N7, U6.D3
PROC_FMC_A11: U1.M7, U6.C4
PROC_FMC_A12: U1.M13, U6.A5
PROC_FMC_A13: U1.M12, U6.B5
PROC_FMC_A14: U1.N12, U6.C5
PROC_FMC_A15: U1.N11, U6.D7
PROC_FMC_A16: U1.N10, U6.D8
PROC_FMC_A17: U1.M10, U6.A7
PROC_FMC_A18: U1.M11, U6.B7
PROC_FMC_A19: U1.A2, U6.C7
PROC_FMC_A20: U1.A1, U6.C8
PROC_FMC_A21: U1.B1, U6.A8
PROC_FMC_A22: U1.B2, U6.G1
PROC_FMC_A23: U1.A3, U6.H8
PROC_FMC_A24: U1.B3, U6.B6
PROC_FMC_CLK: U1.C11, U6.E6
PROC_FMC_D0: U1.L12, U6.F2
PROC_FMC_D1: U1.K13, U6.E2
PROC_FMC_D2: U1.B12, U6.G3
PROC_FMC_D3: U1.C12, U6.E4
PROC_FMC_D4: U1.R8, U6.E5
PROC_FMC_D5: U1.N9, U6.G5
PROC_FMC_D6: U1.P9, U6.G6
PROC_FMC_D7: U1.R9, U6.H7
PROC_FMC_D8: U1.P10, U6.E1
PROC_FMC_D9: U1.R10, U6.E3
PROC_FMC_D10: U1.R12, U6.F3
PROC_FMC_D11: U1.P11, U6.F4
PROC_FMC_D12: U1.R11, U6.F5
PROC_FMC_D13: U1.L15, U6.H5
PROC_FMC_D14: U1.L14, U6.G7
PROC_FMC_D15: U1.K15, U6.E7
PROC_FMC_NE2: R49.1, U1.D9, U6.B4
PROC_FMC_NL: R48.1, U1.B5, U6.F6
PROC_FMC_NOE: R50.1, U1.D11, U6.F8
PROC_FMC_NWAIT: U1.B11, U6.F7
PROC_FMC_NWE: R52.1, U1.C10, U6.G8
PROC_I2S2_CK: U1.D14, U7.24
PROC_I2S2_EXT_SD: U1.C14, U7.25
PROC_I2S2_SD: U1.C13, U7.26
PROC_I2S2_WS: U1.E14, U7.23
PROC_SDIO_CK: R43.1, U1.A12, U5.5
PROC_SDIO_CMD: R42.1, U1.D12, U5.3
PROC_SDIO_D0: R44.1, U1.G14, U5.7
PROC_SDIO_D1: R45.1, U1.F14, U5.8
PROC_SDIO_D2: R46.1, U1.B14, U5.1
PROC_SDIO_D3: R47.1, U1.B13, U5.2
PROC_SYS_JTCK_SWCLK: R25.1, U1.A14, U2.4
PROC_SYS_JTDI: R23.1, U1.A13, U2.8
PROC_SYS_JTDO_SWO: U1.A10, U2.6
PROC_SYS_JTMS_SWDIO: R24.1, U1.A15, U2.2
RST_OUT_U2_JTAG_RST_B: R22.1, U2.10, U27.1
VCC_13V6: C80.1, C84.1, C85.1, J1.1, R74.2, U22.23, U23.1, U23.2, U23.6, U23.7, U24.1, U24.2, U24.6, U24.7
VCC_S1_13V6: C67.1, C74.1, C75.1, R57.2, U19.4, U20.7, U20.13, U20.14, U23.4, U23.5
VCC_S2_13V6: C77.1, R62.2, U21.4, U24.4, U24.5
VCC_TIER1_1V2: C26.1, C57.1, C68.1, R58.1, U1.L11, U7.30, U19.5
VCC_TIER1_3V3: C1.1, C2.1, C3.1, C4.1, C5.1, C6.1, C7.1, C8.1, C9.1, C10.1, C11.1, C12.1, C13.1, C14.1, C15.1, C16.1, C17.1, C18.1, C19.1, C20.1, C21.1, C22.1, C25.1, C32.1, C38.1, C39.1, C42.1, C43.1, C44.1, C45.1, C46.1, C47.1, C58.1, C59.1, C62.1, C63.1, C64.1, C65.1, C72.1, C73.1, C86.1, C87.1, C88.1, C89.1, F1.2, I1.2, I5.2, R7.2, R8.2, R9.2, R10.2, R12.2, R14.2, R16.2, R18.2, R19.2, R21.2, R22.2, R23.2, R24.2, R32.2, R34.2, R35.2, R37.2, R40.2, R42.2, R43.2, R44.2, R45.2, R46.2, R47.2, R48.2, R49.2, R50.2, R51.2, R52.2, R53.2, R55.2, R56.2, R60.1, U1.C1, U1.E7, U1.E8, U1.E9, U1.E10, U1.F4, U1.F5, U1.F11, U1.G5, U1.G11, U1.H5, U1.H11, U1.J5, U1.J11, U1.K5, U1.K11, U1.L7, U1.L8, U1.L9, U1.L10, U2.1, U3.17, U5.4, U6.A6, U6.D5, U6.D6, U6.G4, U6.H3, U7.5, U7.20, U12.A2, U17.4, U18.4, U20.1, U27.5, U28.5, U29.5, U30.5
VCC_TIER2_1V2: C78.1, R63.1, U21.5
